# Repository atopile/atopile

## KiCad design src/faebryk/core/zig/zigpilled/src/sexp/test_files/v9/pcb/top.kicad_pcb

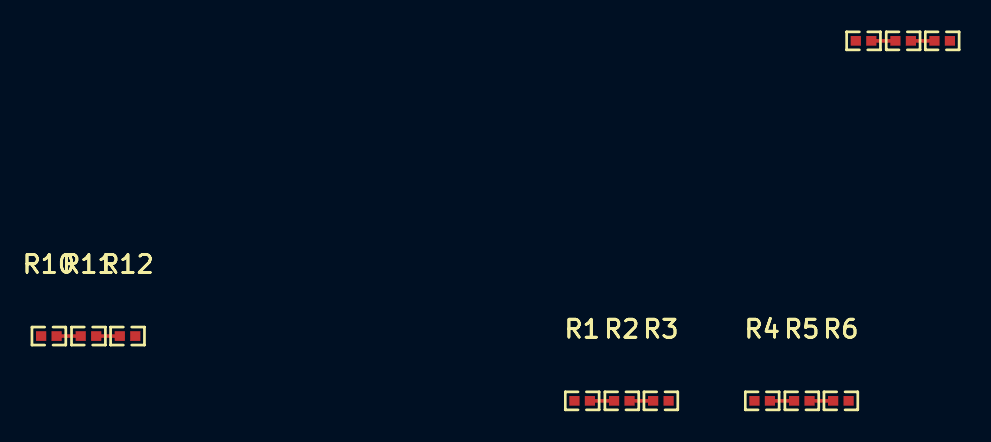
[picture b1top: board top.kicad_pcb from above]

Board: 2 copper layers, 12 parts (0 on the bottom side), 11 nets.

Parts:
R1, R2, R3, R4, R5, R6, R7, R8, R9, R10, R11, R12: 1kΩ ±1% 62.5mW; R0402

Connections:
-net-0: R1.1, R9.2
-net-1: R3.2, R4.1
-net-2: R6.2, R7.1
sub_chains[0]-net-0: R1.2, R2.1
sub_chains[0]-net-1: R2.2, R3.1
sub_chains[1]-net-0: R4.2, R5.1
sub_chains[1]-net-1: R5.2, R6.1
sub_chains[2]-net-0: R7.2, R8.1
sub_chains[2]-net-1: R8.2, R9.1
sub_chains[3]-net-0: R10.2, R11.1
sub_chains[3]-net-1: R11.2, R12.1

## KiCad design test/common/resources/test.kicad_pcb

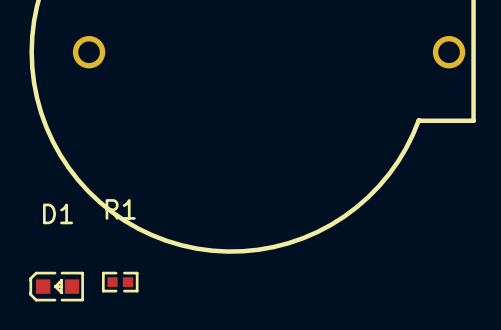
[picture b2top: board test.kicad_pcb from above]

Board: 2 copper layers, 3 parts (0 on the bottom side), 3 nets, no tracks yet.

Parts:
B1: ButtonCell; BAT-TH_BS-02-A1AJ010
D1: LED; LED0603-RD-YELLOW
R1: 40.2Ω; R0402

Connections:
B1-1-R1-2: B1.1, R1.2
B1-2-D1-2: B1.2, D1.2
D1-1-R1-1: D1.1, R1.1
